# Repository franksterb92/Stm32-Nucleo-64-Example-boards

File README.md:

# Stm32-Nucleo-64-Example-boards
some boards made with kicad that are meant to go alone with STM32 Arm Programming for Embeded Systems Book

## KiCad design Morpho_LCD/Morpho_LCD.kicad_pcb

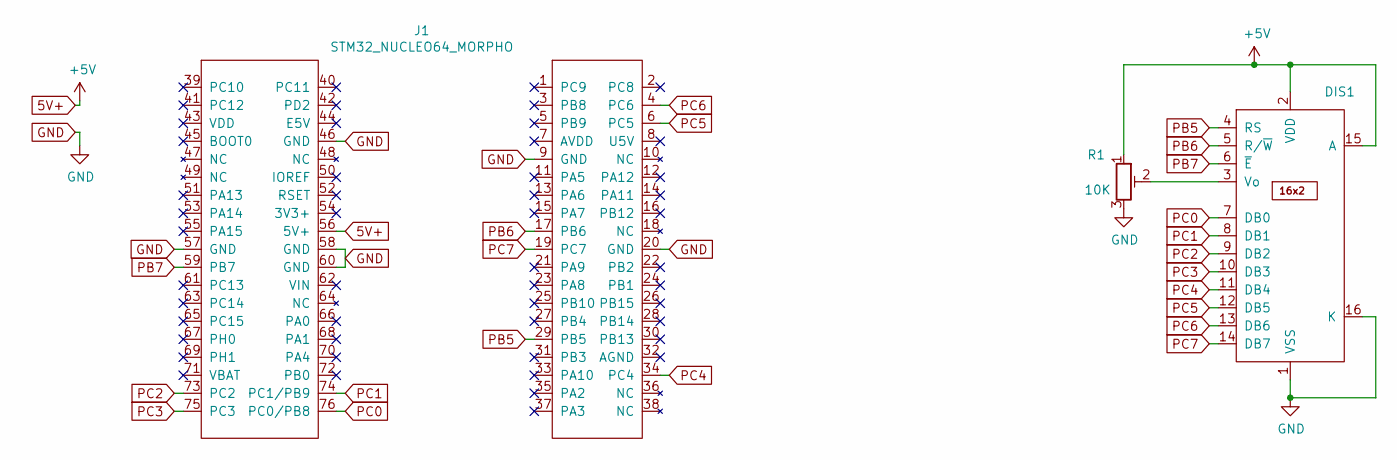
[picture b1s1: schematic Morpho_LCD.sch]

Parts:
DIS1: 16x2_Display_parallel; WC1602A
J1: STM32_NUCLEO64_MORPHO; Morpho_Without_Arduino
R1: 10K; Potentiometer_Bourns_3386P_Vertical

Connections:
5V+: DIS1.2 (VDD), DIS1.15 (A), J1.56 (5V+), R1.1
GND: DIS1.1 (VSS), DIS1.16 (K), J1.9 (GND), J1.20 (GND), J1.46 (GND), J1.57 (GND), J1.58 (GND), J1.60 (GND), R1.3
unnamed: DIS1.3 (Vo), R1.2
PB5: DIS1.4 (RS), J1.29 (PB5)
PB6: DIS1.5 (R/~W), J1.17 (PB6)
PB7: DIS1.6 (~E), J1.59 (PB7)
PC0: DIS1.7 (DB0), J1.76 (PC0/PB8)
PC1: DIS1.8 (DB1), J1.74 (PC1/PB9)
PC2: DIS1.9 (DB2), J1.73 (PC2)
PC3: DIS1.10 (DB3), J1.75 (PC3)
PC4: DIS1.11 (DB4), J1.34 (PC4)
PC5: DIS1.12 (DB5), J1.6 (PC5)
PC6: DIS1.13 (DB6), J1.4 (PC6)
PC7: DIS1.14 (DB7), J1.19 (PC7)

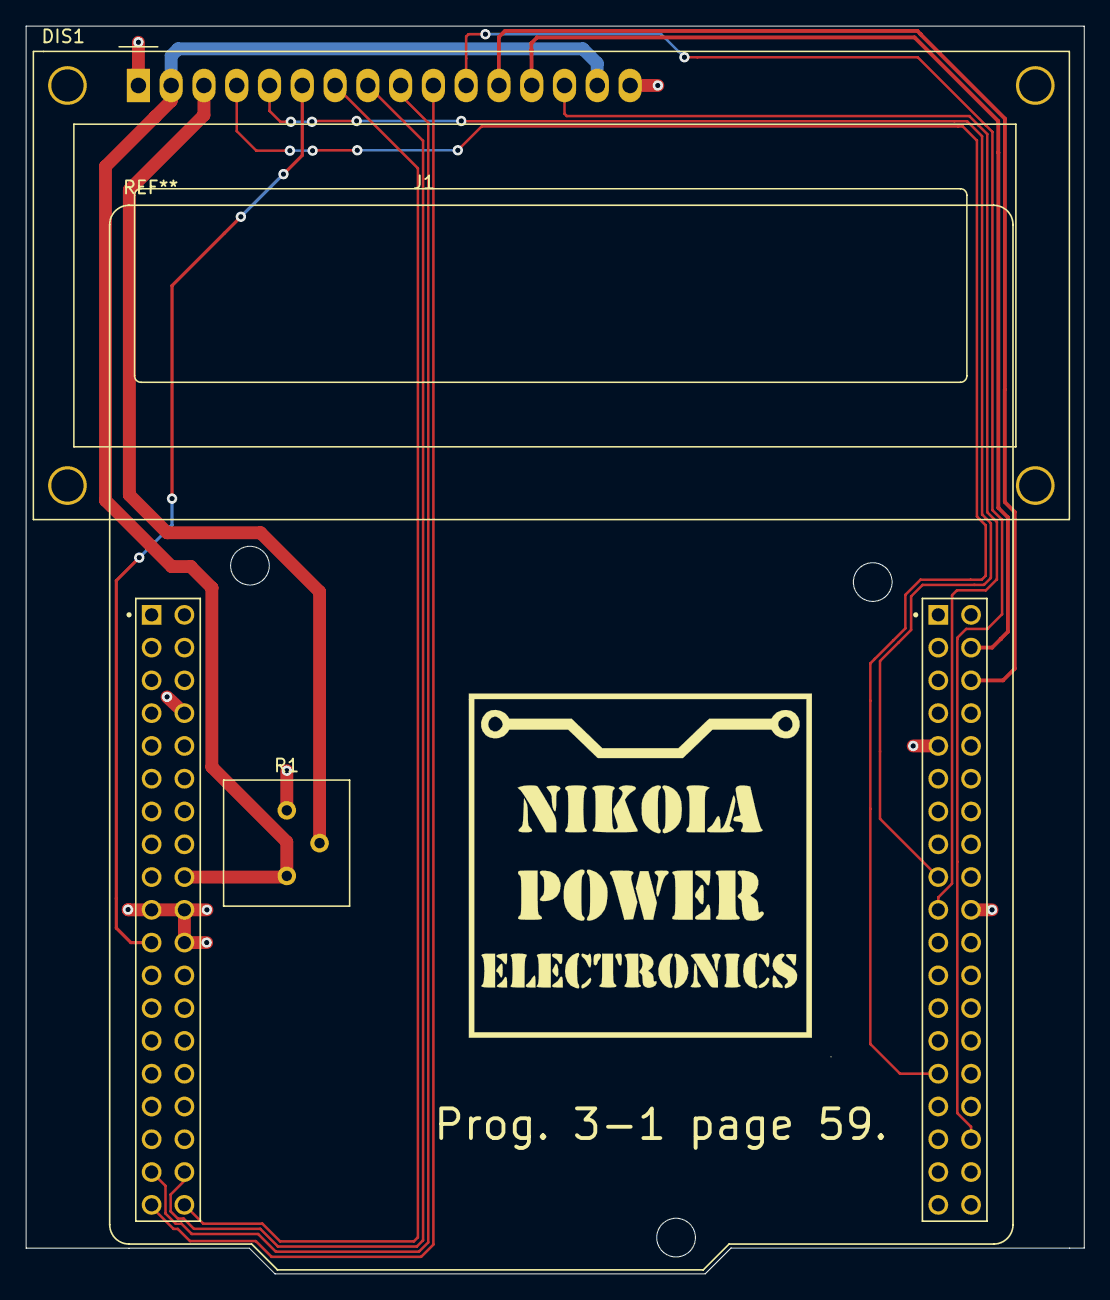
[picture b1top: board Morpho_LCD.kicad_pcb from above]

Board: 2 copper layers, 82.0 x 96.7 mm, 3 parts (0 on the bottom side), 14 nets.

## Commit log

2021-12-24 Lcd Boards kicad flies
